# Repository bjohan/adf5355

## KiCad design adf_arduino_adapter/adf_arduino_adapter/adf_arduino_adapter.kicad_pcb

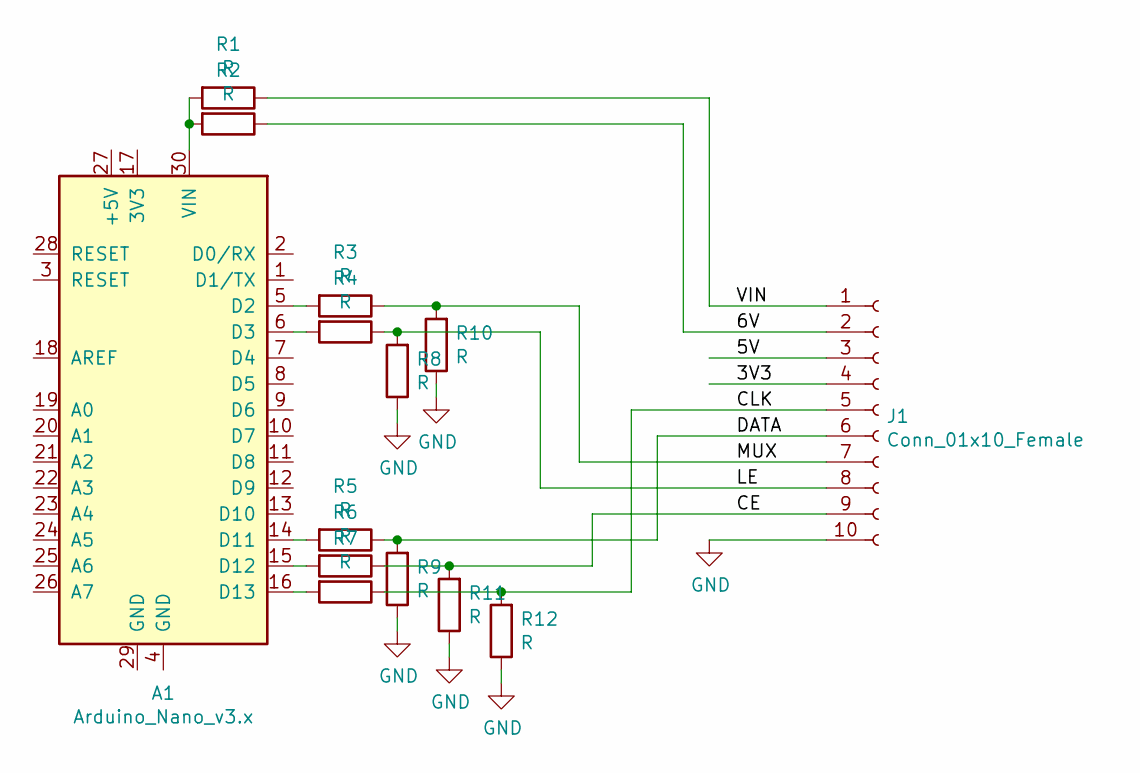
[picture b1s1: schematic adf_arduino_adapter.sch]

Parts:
A1: Arduino_Nano_v3.x; Arduino_Nano
J1: Conn_01x10_Female; Molex_KK-254_AE-6410-10A_1x10_P2.54mm_Vertical
R1, R2, R3, R4, R5, R6, R7, R8, R9, R10, R11, R12: R; R_1206_3216Metric_Pad1.42x1.75mm_HandSolder

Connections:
/3V3: J1.4
/5V: J1.3
/6V: J1.2, R2.1
/CE: J1.9, R6.1, R11.2
/CLK: J1.5, R7.1, R12.2
/DATA: J1.6, R5.1, R9.2
/LE: J1.8, R4.1, R8.2
/MUX: J1.7, R3.1, R10.2
/VIN: J1.1, R1.1
GND: J1.10, R8.1, R9.1, R10.1, R11.1, R12.1
unnamed: A1.5 (D2), R3.2
unnamed: A1.6 (D3), R4.2
unnamed: A1.14 (D11), R5.2
unnamed: A1.15 (D12), R6.2
unnamed: A1.16 (D13), R7.2
unnamed: A1.30 (VIN), R1.2, R2.2

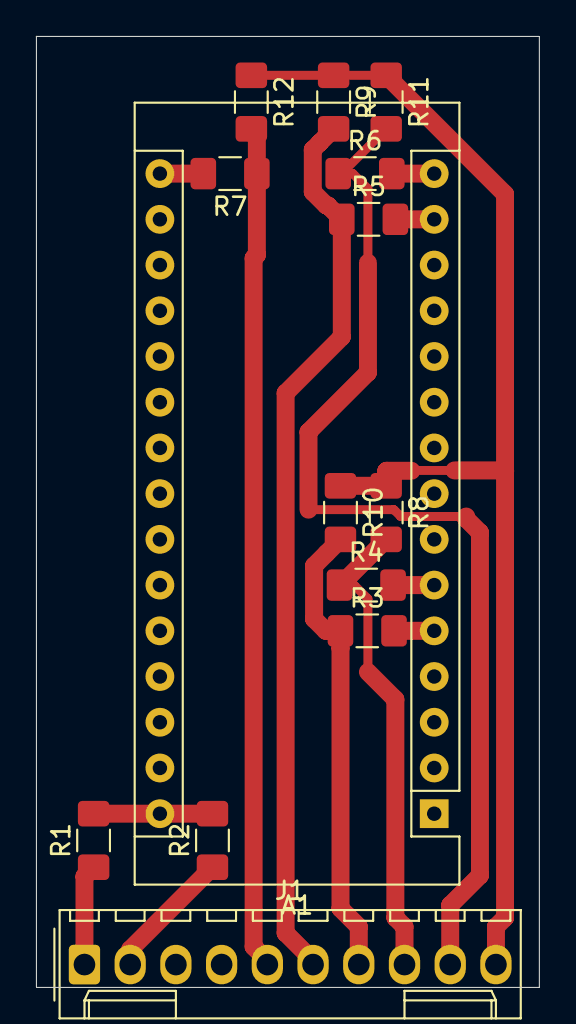
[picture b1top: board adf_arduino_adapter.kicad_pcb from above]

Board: 2 copper layers, 27.9 x 52.8 mm, 14 parts (0 on the bottom side), 14 nets.

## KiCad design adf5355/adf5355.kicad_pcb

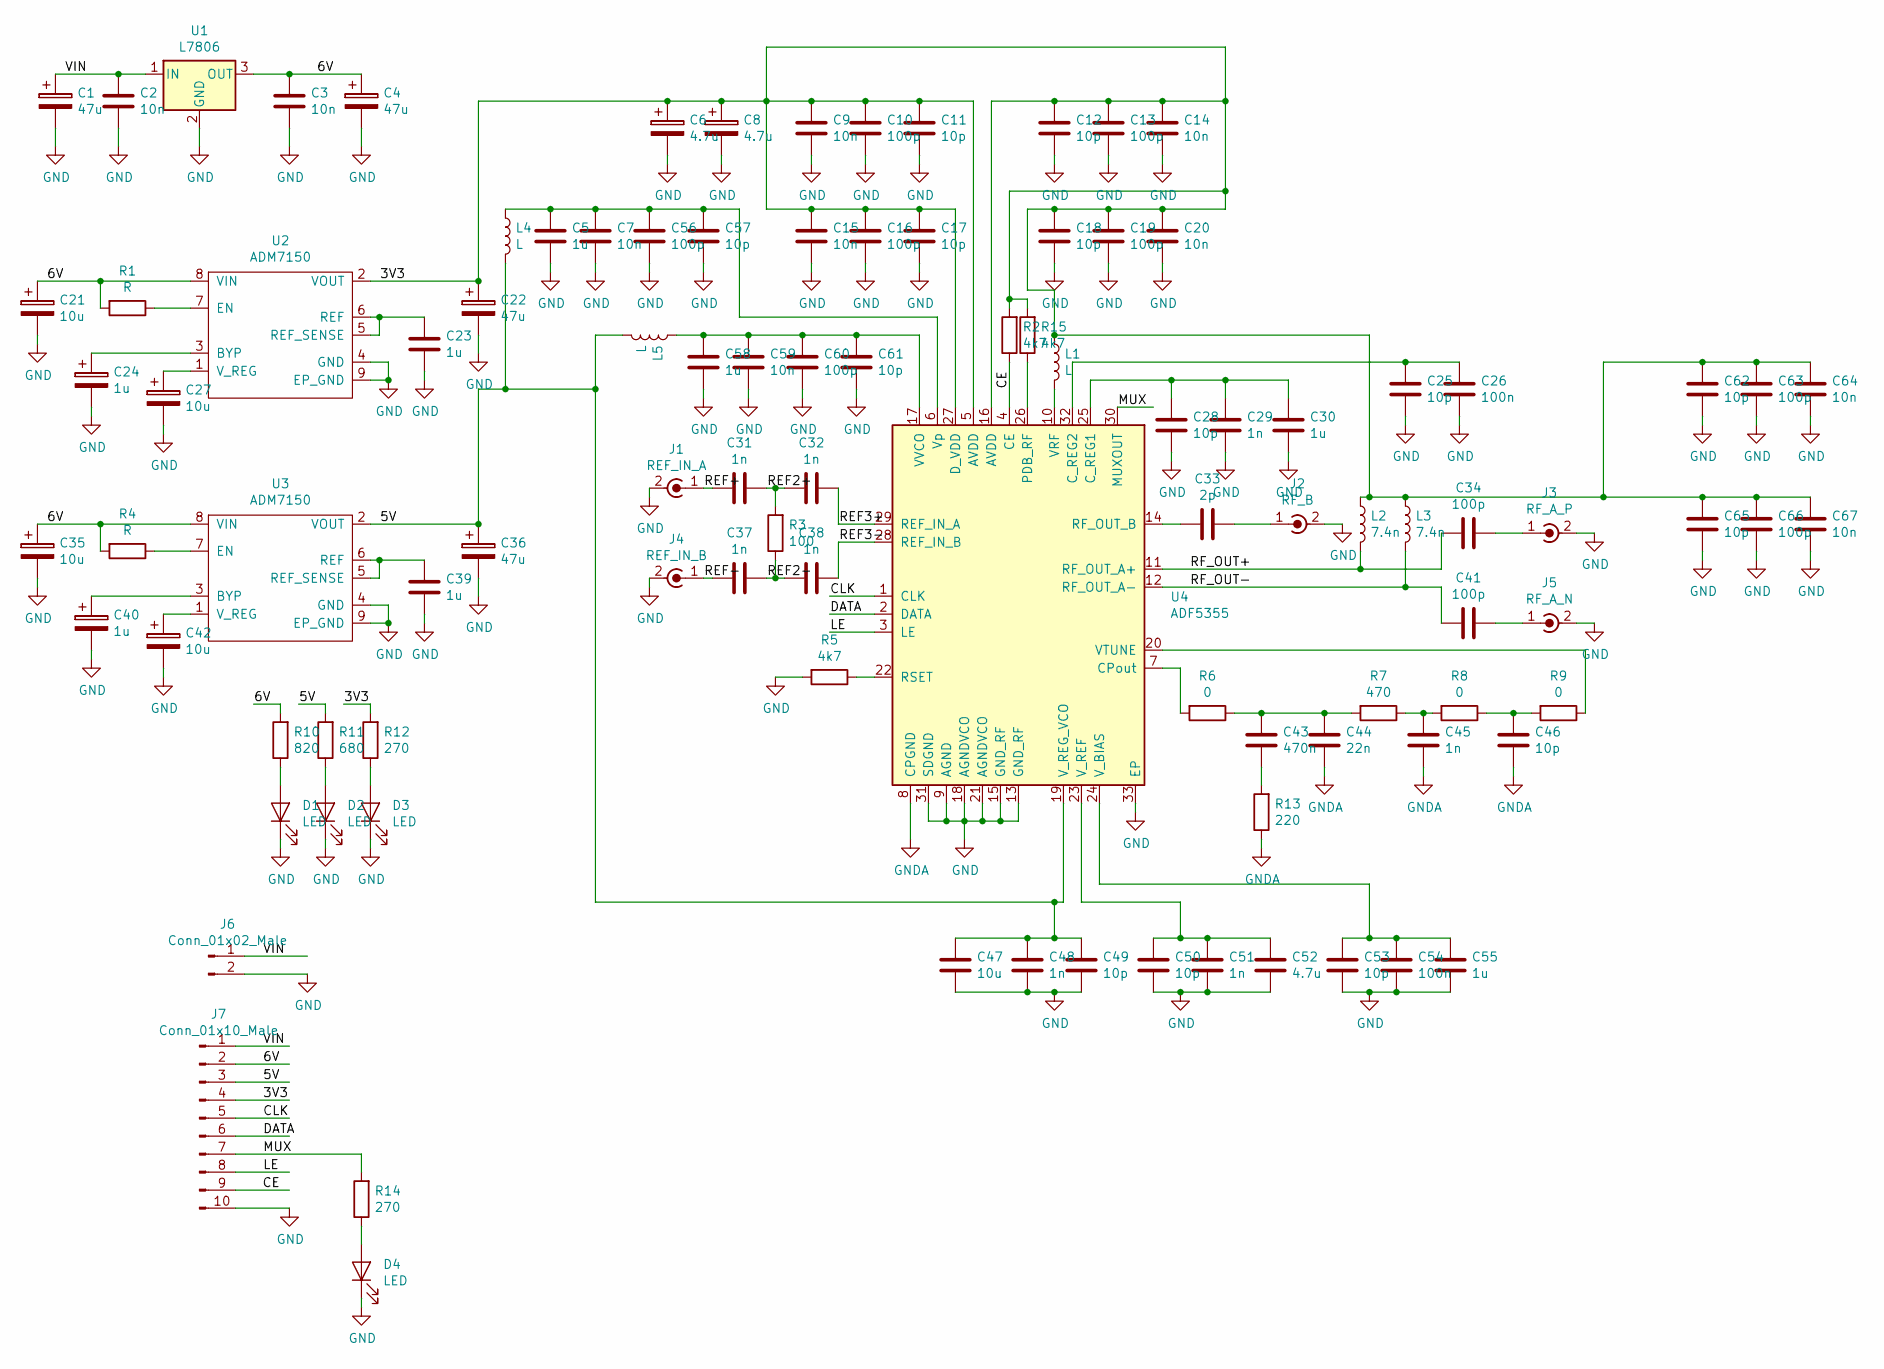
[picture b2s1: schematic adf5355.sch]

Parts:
C1, C4, C22, C36: 47u; CP_Elec_4x4.5
C2, C3: 10n; C_0805
C5, C30, C55, C58: 1u; C_0603
C6, C8: 4.7u; C_1812
C7, C9, C14, C15, C20, C59, C64, C67: 10n; C_0603
C10, C13, C16, C19, C34, C41, C56, C60, C63, C66: 100p; C_0603
C11, C12, C17, C18, C25, C28, C46, C49, C50, C53, C57, C61, C62, C65: 10p; C_0603
C21, C27, C35, C42, C47: 10u; C_1812
C23, C24, C39, C40: 1u; C_1206
C26, C54: 100n; C_0603
C29, C31, C32, C37, C38, C45, C48, C51: 1n; C_0603
C33: 2p; C_0603
C43: 470n; C_0603
C44: 22n; C_0603
C52: 4.7u; C_0603
D1, D2, D3, D4: LED; LED_0805
J1: REF_IN_A; SMA_THT_Jack_Straight
J2: RF_B; SMA_THT_Jack_Straight
J3: RF_A_P; SMA_THT_Jack_Straight
J4: REF_IN_B; SMA_THT_Jack_Straight
J5: RF_A_N; SMA_THT_Jack_Straight
J6: Conn_01x02_Male; Molex_KK-6410-02_02x2.54mm_Straight
J7: Conn_01x10_Male; Molex_KK-6410-10_10x2.54mm_Straight
L1, L4, L5: L; C_0805_HandSoldering
L2, L3: 7.4n; C_0805_HandSoldering
R1, R4: R; R_0805
R2, R5, R15: 4k7; R_0805
R3: 100; R_0805
R6, R8, R9: 0; R_0603
R7: 470; R_0603
R10: 820; R_0805
R11: 680; R_0805
R12, R14: 270; R_0805
R13: 220; R_0603
U1: L7806; TO-220-3_Vertical
U2, U3: ADM7150; SOIC-8-1EP_3.9x4.9mm_Pitch1.27mm
U4: ADF5355; LFCSP-32-1EP_5x5mm_P0.5mm_EP3.25x3.25mm

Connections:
/3V3: C6.1, C8.1, C9.1, C10.1, C11.1, C12.1, C13.1, C14.1, C15.1, C16.1, C17.1, C18.1, C19.1, C20.1, C22.1, C62.1, C63.1, C64.1, C65.1, C66.1, C67.1, J7.4, L1.1, L2.1, L3.1, R2.2, R12.2, R15.2, U2.2 (VOUT), U4.5 (AVDD), U4.16 (AVDD), U4.27 (D_VDD)
/5V: C36.1, C47.1, C48.1, C49.1, J7.3, L4.2, L5.2, R11.2, U3.2 (VOUT), U4.19 (V_REG_VCO)
/6V: C3.1, C4.1, C21.1, C35.1, J7.2, R1.2, R4.2, R10.2, U1.3 (OUT), U2.8 (VIN), U3.8 (VIN)
/CE: J7.9, R2.1, U4.4 (CE)
/CLK: J7.5, U4.1 (CLK)
/DATA: J7.6, U4.2 (DATA)
/LE: J7.8, U4.3 (LE)
/MUX: J7.7, R14.2, U4.30 (MUXOUT)
/REF2+: C31.1, C32.2, R3.2
/REF2-: C37.1, C38.2, R3.1
/REF3+: C32.1, U4.29 (REF_IN_A)
/REF3-: C38.1, U4.28 (REF_IN_B)
/REF+: C31.2, J1.1 (In)
/REF-: C37.2, J4.1 (In)
/RF_OUT+: C34.2, L2.2, U4.11 (RF_OUT_A+)
/RF_OUT-: C41.2, L3.2, U4.12 (RF_OUT_A-)
/VIN: C1.1, C2.1, J6.1, J7.1, U1.1 (IN)
GND: C1.2, C2.2, C3.2, C4.2, C5.2, C6.2, C7.2, C8.2, C9.2, C10.2, C11.2, C12.2, C13.2, C14.2, C15.2, C16.2, C17.2, C18.2, C19.2, C20.2, C21.2, C22.2, C23.2, C24.2, C25.2, C26.2, C27.2, C28.2, C29.2, C30.2, C35.2, C36.2, C39.2, C40.2, C42.2, C47.2, C48.2, C49.2, C50.2, C51.2, C52.2, C53.2, C54.2, C55.2, C56.2, C57.2, C58.2, C59.2, C60.2, C61.2, C62.2, C63.2, C64.2, C65.2, C66.2, C67.2, D1.1 (K), D2.1 (K), D3.1 (K), D4.1 (K), J1.2 (Ext), J2.2 (Ext), J3.2 (Ext), J4.2 (Ext), J5.2 (Ext), J6.2, J7.10, R5.2, U1.2 (GND), U2.4 (GND), U2.9 (EP_GND), U3.4 (GND), U3.9 (EP_GND), U4.9 (AGND), U4.13 (GND_RF), U4.15 (GND_RF), U4.18 (AGNDVCO), U4.21 (AGNDVCO), U4.31 (SDGND), U4.33 (EP)
GNDA: C44.2, C45.2, C46.2, R13.1, U4.8 (CPGND)
unnamed: C5.1, C7.1, C56.1, C57.1, L4.1, U4.6 (Vp)
unnamed: C23.1, U2.5 (REF_SENSE), U2.6 (REF)
unnamed: C24.1, U2.3 (BYP)
unnamed: C25.1, C26.1, U4.32 (C_REG2)
unnamed: C27.1, U2.1 (V_REG)
unnamed: C28.1, C29.1, C30.1, U4.25 (C_REG1)
unnamed: C33.1, J2.1 (In)
unnamed: C33.2, U4.14 (RF_OUT_B)
unnamed: C34.1, J3.1 (In)
unnamed: C39.1, U3.5 (REF_SENSE), U3.6 (REF)
unnamed: C40.1, U3.3 (BYP)
unnamed: C41.1, J5.1 (In)
unnamed: C42.1, U3.1 (V_REG)
unnamed: C43.1, C44.1, R6.1, R7.2
unnamed: C43.2, R13.2
unnamed: C45.1, R7.1, R8.2
unnamed: C46.1, R8.1, R9.2
unnamed: C50.1, C51.1, C52.1, U4.23 (V_REF)
unnamed: C53.1, C54.1, C55.1, U4.24 (V_BIAS)
unnamed: C58.1, C59.1, C60.1, C61.1, L5.1, U4.17 (VVCO)
unnamed: D1.2 (A), R10.1
unnamed: D2.2 (A), R11.1
unnamed: D3.2 (A), R12.1
unnamed: D4.2 (A), R14.1
unnamed: L1.2, U4.10 (VRF)
unnamed: R1.1, U2.7 (EN)
unnamed: R4.1, U3.7 (EN)
unnamed: R5.1, U4.22 (RSET)
unnamed: R6.2, U4.7 (CPout)
unnamed: R9.1, U4.20 (VTUNE)
unnamed: R15.1, U4.26 (PDB_RF)

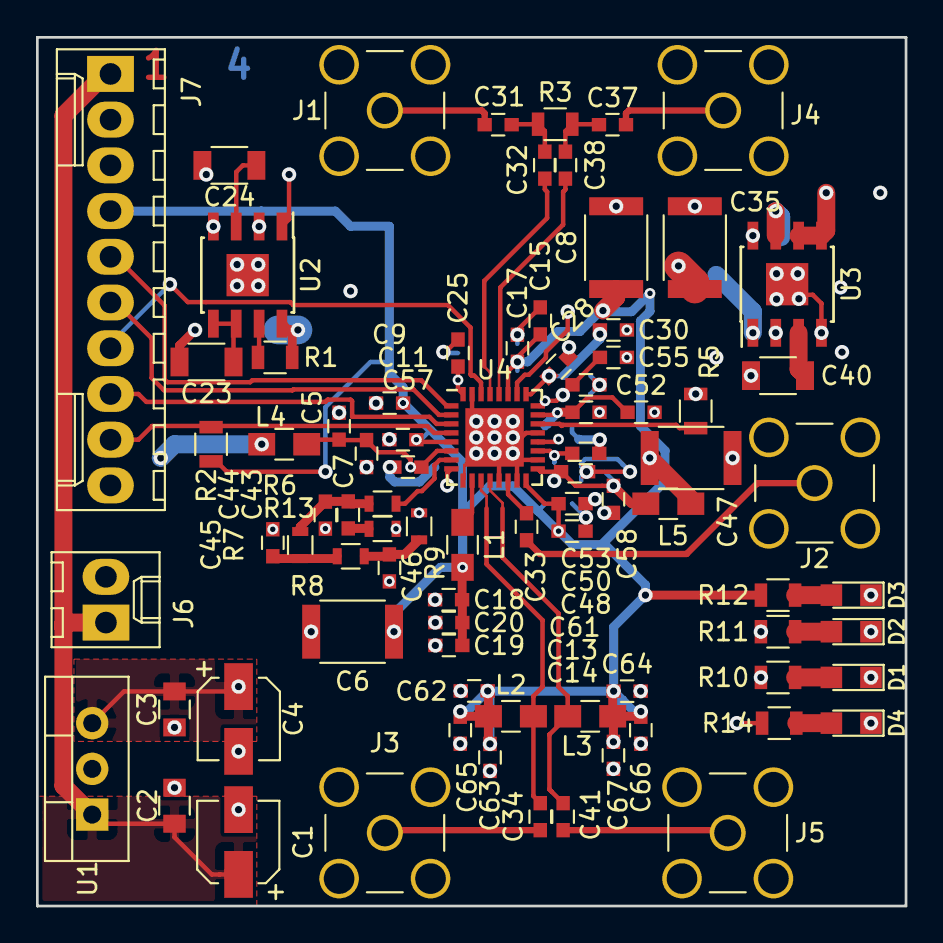
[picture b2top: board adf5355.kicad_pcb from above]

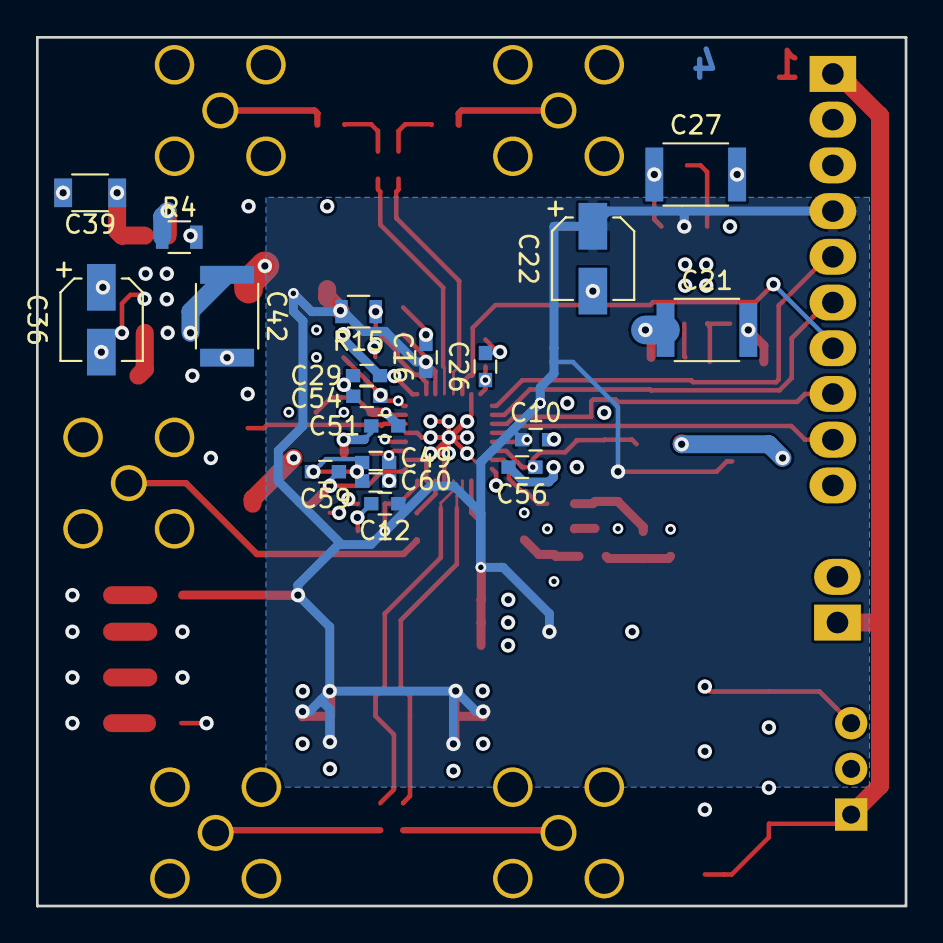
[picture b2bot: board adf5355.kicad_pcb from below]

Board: 4 copper layers, 48.3 x 48.3 mm, 102 parts (19 on the bottom side), 50 nets.

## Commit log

2018-10-11 Initial checkin
2018-10-14 Placing more components
2018-10-15 More layout placement
2018-10-16 More placing
2018-10-18 More work on layout, decided to switch to four layer board
2018-10-22 Started routing
2018-10-24 Placement of LDOs and components
2018-10-29 More layout
2018-12-13 More
2018-12-16 Layout fully routed, now needs finilizing, moving vias to make better powerplanes, route diffpairs properly etc.
2018-12-23 Added some capacitors, better power planes etc. Needs fixing transmission lines and checking component placement for solderability. Also the c_reg capacitors probably needs to be closer to the pin
2018-12-23 Added power plane for coarse input regulator
2018-12-23 Fixed transmission line widths
2018-12-26 Added layer markings
2019-01-26 Found via that caused DRC error at manufacturer
2019-01-26 Fixed silk screen and added files sent for production
2019-04-21 Addded adapterboard
2019-04-23 Started writing sketch, current version can blink the muxout led
2019-04-23 Added more registers
2019-04-23 Now all registers are added
2019-04-25 Now locks, and frequency can be changed, but still very crude
2019-04-26 more testing
2019-04-28 More!
2019-04-29 Simple sweep
2019-05-01 more frac n
2022-11-22 Added python script
2022-11-22 Added arduino fw
2022-11-23 cleaned prints
